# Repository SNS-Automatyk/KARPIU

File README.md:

# Projekt K.A.R.P.I.U
Knowledge Acquisition and Rapid Problem Intervention Unit

# hierarchia projektu:
## Schematy -> w tym folderze znajdują się schematy w .jpg jak i również w kicad 
## obudowa ->  w folderze znajduje się projekt obudowy jest on do modyfikacji.
## micropython -> w tym folderze znajduje się gotowy kod dla projektu, w podfoldrze można zaleźć pliki audio jak i zarówno pliki z naszymi bibliotekami.

# zależności jakie trzeba zainstalować jeśli ktoś by chciał zmieniać oprogramowanie.

## w thonny IDE dajemy narzędzia -> zarządzaj pakietami i szukamy następujących pakietów:
### machine, network, uos, os, umail, base64, neopixel, 

# W folderze micropython jest plik "KARPIU_FINAL.py" jest to finalna wersja projektu i aktualna do tej pory, reszty plików na dzień 03.08.2026r. nie jesteśmy w stanie wrzucić ponieważ nikt nie chce przyjść otworzyć koła :)))

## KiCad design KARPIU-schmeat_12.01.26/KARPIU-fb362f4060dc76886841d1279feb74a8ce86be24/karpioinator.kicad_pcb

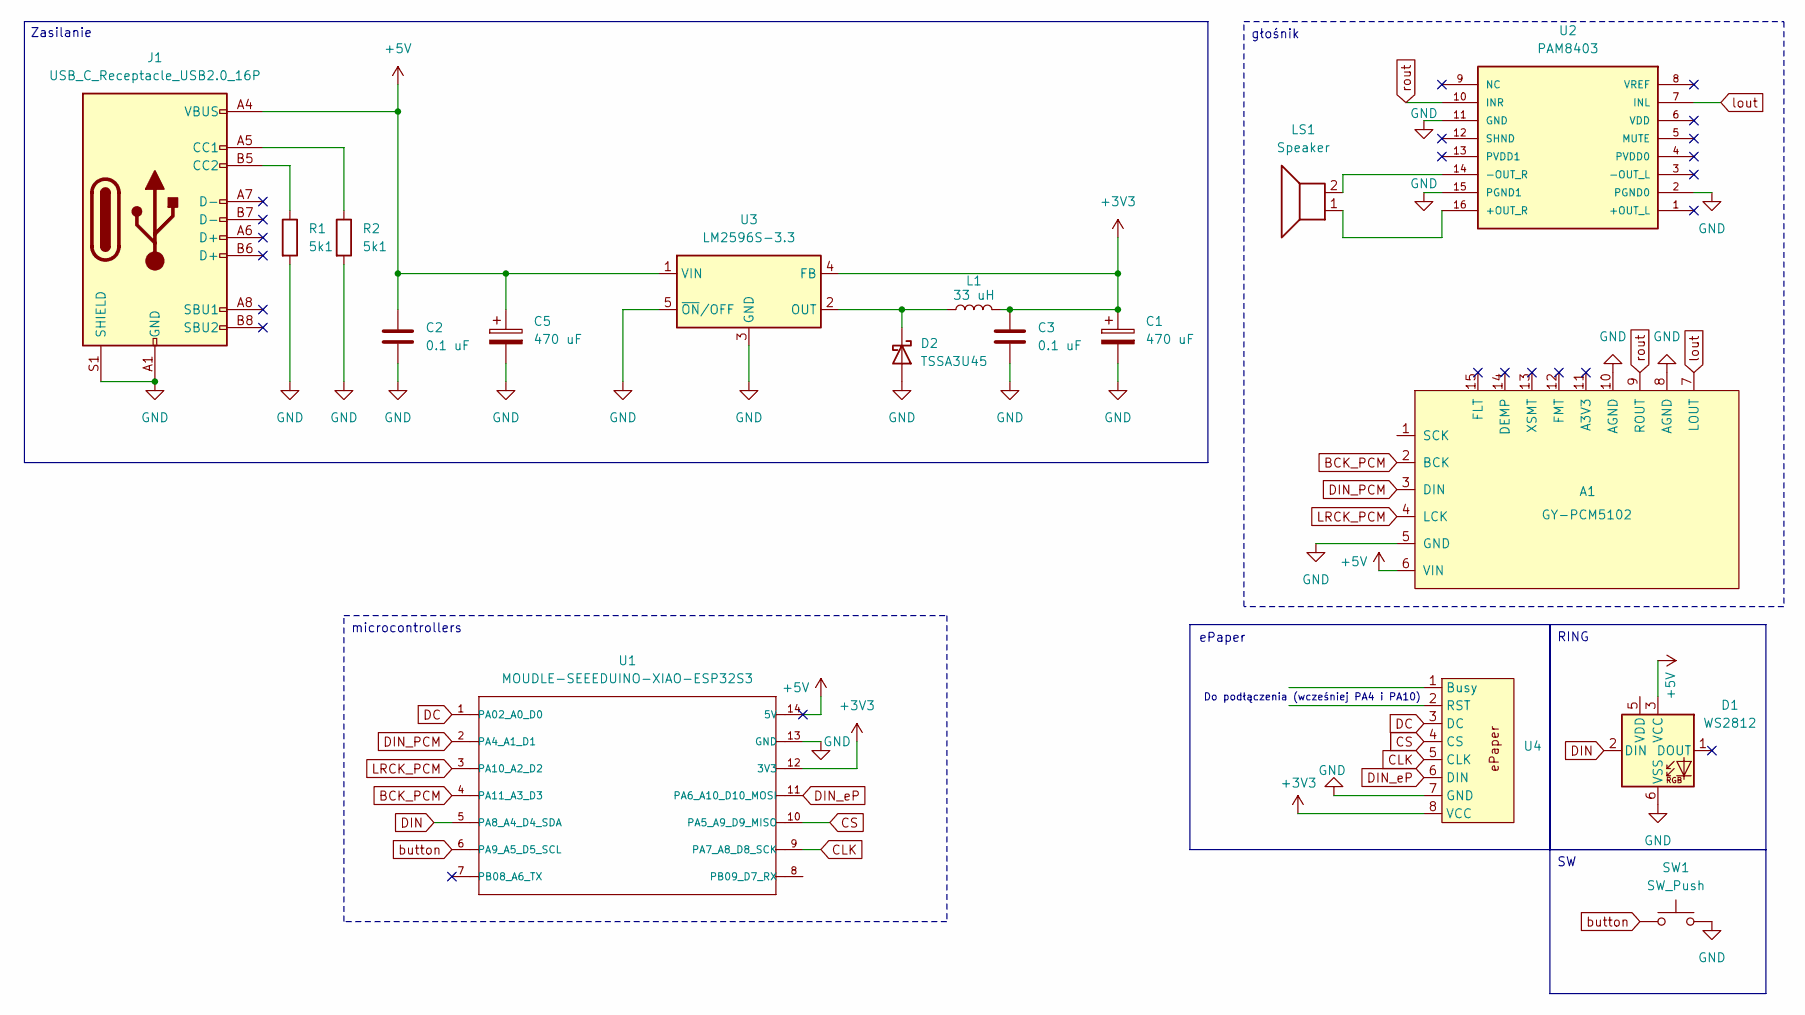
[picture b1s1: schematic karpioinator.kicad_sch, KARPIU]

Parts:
A1: GY-PCM5102; GY-PCM5102 (1)
C1: 470 uF; C_Axial_L3.8mm_D2.6mm_P7.50mm_Horizontal
C2, C3: 0.1 uF; C_Axial_L3.8mm_D2.6mm_P7.50mm_Horizontal
C5: 470 uF; CP_Axial_L11.0mm_D5.0mm_P18.00mm_Horizontal
D1: WS2812; PinSocket_1x06_P2.54mm_Horizontal
D2: TSSA3U45; D_0603_1608Metric_Pad1.05x0.95mm_HandSolder
J1: USB_C_Receptacle_USB2.0_16P; USB_C_Receptacle_G-Switch_GT-USB-7010ASV
L1: 33 uH; L_7.3x7.3_H3.5
LS1: Speaker
R1, R2: 5k1; R_Axial_DIN0204_L3.6mm_D1.6mm_P2.54mm_Vertical
SW1: SW_Push; PinSocket_1x02_P2.54mm_Vertical
U1: MOUDLE-SEEEDUINO-XIAO-ESP32S3; XIAO-ESP32S3-DIP
U2: PAM8403; PinSocket_1x16_P2.54mm_Vertical_SMD_Pin1Left
U3: LM2596S-3.3; TO-263-5_TabPin3
U4: PinSocket_1x08_P2.54mm_Vertical

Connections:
+3V3: C1.1, C3.1, L1.2, U1.12 (3V3), U3.4 (FB), U4.8 (VCC)
+5V: A1.6 (VIN), C2.1, C5.1, D1.3 (VCC), J1.A4 (VBUS), J1.A9 (VBUS), J1.B4 (VBUS), J1.B9 (VBUS), U1.14 (5V), U3.1 (VIN)
BCK_PCM: A1.2 (BCK), U1.4 (PA11_A3_D3)
CLK: U1.9 (PA7_A8_D8_SCK), U4.5 (CLK)
CS: U1.10 (PA5_A9_D9_MISO), U4.4 (CS)
DC: U1.1 (PA02_A0_D0), U4.3 (DC)
DIN: D1.2 (DIN), U1.5 (PA8_A4_D4_SDA)
DIN_PCM: A1.3 (DIN), U1.2 (PA4_A1_D1)
DIN_eP: U1.11 (PA6_A10_D10_MOSI), U4.6 (DIN)
GND: A1.5 (GND), A1.8 (AGND), A1.10 (AGND), C1.2, C2.2, C3.2, C5.2, D1.6 (VSS), D2.2 (A), J1.A1 (GND), J1.A12 (GND), J1.B1 (GND), J1.B12 (GND), J1.S1 (SHIELD), R1.2, R2.2, SW1.2, U1.13 (GND), U2.2 (PGND0), U2.11 (GND), U2.15 (PGND1), U3.3 (GND), U3.5 (~ON/OFF), U4.7 (GND)
LRCK_PCM: A1.4 (LCK), U1.3 (PA10_A2_D2)
unnamed: D2.1 (K), L1.1, U3.2 (OUT)
unnamed: J1.A5 (CC1), R2.1
unnamed: J1.B5 (CC2), R1.1
unnamed: LS1.1, U2.16 (+OUT_R)
unnamed: LS1.2, U2.14 (-OUT_R)
button: SW1.1, U1.6 (PA9_A5_D5_SCL)
lout: A1.7 (LOUT), U2.7 (INL)
rout: A1.9 (ROUT), U2.10 (INR)

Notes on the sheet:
Do podłączenia (wcześniej PA4 i PA10)
ePaper
Zasilanie
microcontrollers
głośnik
RING

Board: 2 copper layers, 16 parts (0 on the bottom side), 17 nets, no tracks yet.

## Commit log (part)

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2024-11-23 Add test camera files
2024-12-13 dodano aktualizacje kodu do obslugi kamery oraz dodano esptool zeby mozna bylo wgrac oprogramowanie
2025-01-10 wysylanie + modul umail
2025-01-10 haslo do wifi
2025-01-13 utworzony głowny plik 'karpiu.py' zawierający połączone elementy
2025-01-31 Dodanie pliku ze wzorem jak ma wyglądać załączanie
2025-03-11 Add files via upload
    przepisanie od nowa, moze zadziała pls pls pls
2025-04-29 Create działa_już
2025-05-06 Update działa_już
2025-07-06 Update KARPIU.py
    dodano działającą wersję obsługi kamery wraz z wysyłaniem maila :)
2025-08-11 Create button_test_dirty_one
    testing button by this script
2026-01-11 dodano nowy schemat oraz pliki z footprintami
2026-01-12 Dodano zasilanie
    Do sprawdzenia podłączenia ePaper i zasilanie ringa, ew. sprawdzenie czy pozostałe komenenty nie potrzebują dodatkowych elemnetów oraz dodanie footprintów jeśli ma być płytka PCB
2026-01-12 poprawiono schemat oraz rozpoczęto pcb
2026-01-22 Dodanie zabezpieczeń i elementów stabilizujących prace
2026-03-05 Schemat 5.03
